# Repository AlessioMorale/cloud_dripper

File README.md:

# cloud_dripper
An ESP32-based indoor watering controller

Link to [Interactive BOM](https://htmlpreview.github.io/?https://github.com/AlessioMorale/cloud_dripper/blob/main/docs/index.html)

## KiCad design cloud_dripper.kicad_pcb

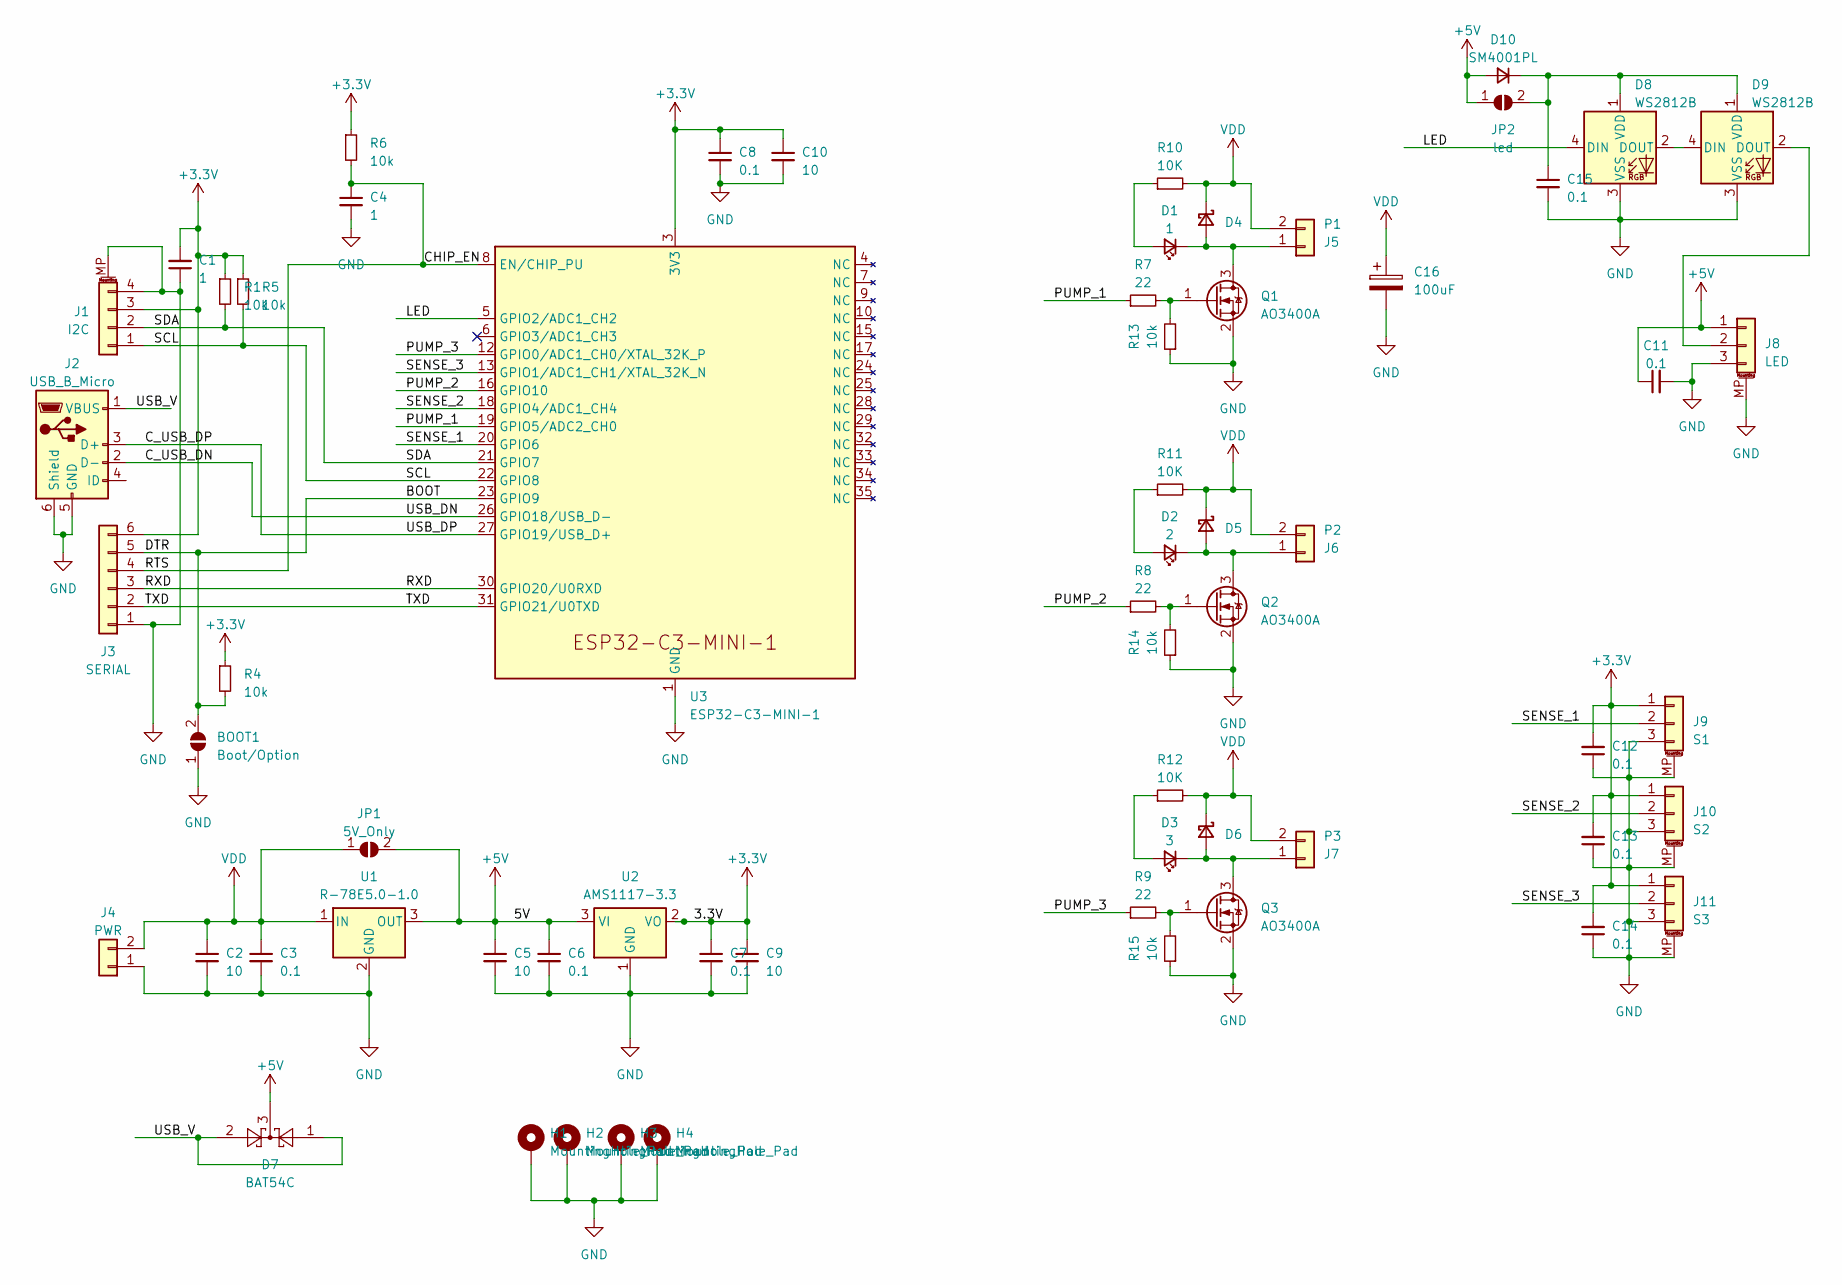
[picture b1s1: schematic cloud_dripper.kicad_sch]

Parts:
BOOT1: Boot/Option; SolderJumper-2_P1.3mm_Open_RoundedPad1.0x1.5mm
C1, C4: 1; C_0402_1005Metric; JLCPCB C52923
C2, C5, C9, C10: 10; C_0805_2012Metric; JLCPCB C15850
C3, C6, C7, C8, C11, C12, C13, C14, C15: 0.1; C_0402_1005Metric; JLCPCB C1525
C16: 100uF; CP_Elec_6.3x5.8
D1: 1; LED_0805_2012Metric; JLCPCB C2297
D2: 2; LED_0805_2012Metric; JLCPCB C2297
D3: 3; LED_0805_2012Metric; JLCPCB C2297
D4, D5, D6: D_SMA; JLCPCB C22452
D7: BAT54C; SOT-23
D8, D9: WS2812B; LED_WS2812B-2020_PLCC4_2.0x2.0mm
D10: SM4001PL; D_SOD-123F; JLCPCB C64898
H1, H2, H3, H4: MountingHole_Pad; MountingHole_2.2mm_M2_Pad
J1: I2C; JST_SH_BM04B-SRSS-TB_1x04-1MP_P1.00mm_Vertical
J2: USB_B_Micro; USB_Micro-B_Molex_47346-0001
J3: SERIAL; PinHeader_2x03_P2.54mm_Vertical
J4: PWR; Molex_Micro-Fit_3.0_43045-0200_2x01_P3.00mm_Horizontal
J5: P1; PinHeader_1x02_P2.54mm_Vertical
J6: P2; PinHeader_1x02_P2.54mm_Vertical
J7: P3; PinHeader_1x02_P2.54mm_Vertical
J8: LED; JST_SH_BM03B-SRSS-TB_1x03-1MP_P1.00mm_Vertical
J9: S1; JST_SH_BM03B-SRSS-TB_1x03-1MP_P1.00mm_Vertical
J10: S2; JST_SH_BM03B-SRSS-TB_1x03-1MP_P1.00mm_Vertical
J11: S3; JST_SH_BM03B-SRSS-TB_1x03-1MP_P1.00mm_Vertical
JP1: 5V_Only; SolderJumper-2_P1.3mm_Open_RoundedPad1.0x1.5mm
JP2: led; SolderJumper-2_P1.3mm_Open_RoundedPad1.0x1.5mm
Q1, Q2, Q3: AO3400A; SOT-23; JLCPCB C20917
R1, R4, R5, R6, R13, R14, R15: 10k; R_0402_1005Metric; JLCPCB C25744
R7, R8, R9: 22; R_0402_1005Metric; JLCPCB C25092
R10, R11, R12: 10K; R_0402_1005Metric; JLCPCB C25744
U1: R-78E5.0-1.0; Converter_DCDC_RECOM_R-78E-0.5_THT
U2: AMS1117-3.3; SOT-223-3_TabPin2; JLCPCB C6186
U3: ESP32-C3-MINI-1; JLCPCB C2838502

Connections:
+3.3V: C1.2, C7.1, C8.1, C9.1, C10.1, C12.2, C13.2, C14.2, J1.3, J3.6, J9.1, J10.1, J11.1, R1.1, R4.1, R5.1, R6.1, U2.2 (VO), U3.3 (3V3)
+5V: C5.1, C6.1, C11.1, D7.3, D10.2 (A), J8.1, JP1.2 (B), JP2.1 (A), U1.3 (OUT), U2.3 (VI)
/BOOT: BOOT1.2 (B), J3.5, R4.2, U3.23 (GPIO9)
/CHIP_EN: C4.1, J3.4, R6.2, U3.8 (EN/CHIP_PU)
/C_USB_DN: J2.2 (D-), U3.26 (GPIO18/USB_D-)
/C_USB_DP: J2.3 (D+), U3.27 (GPIO19/USB_D+)
/LED: D8.4 (DIN), U3.5 (GPIO2/ADC1_CH2)
/PUMP_1: R7.1, U3.19 (GPIO5/ADC2_CH0)
/PUMP_2: R8.1, U3.16 (GPIO10)
/PUMP_3: R9.1, U3.12 (GPIO0/ADC1_CH0/XTAL_32K_P)
/RXD: J3.3, U3.30 (GPIO20/U0RXD)
/SCL: J1.1, R5.2, U3.22 (GPIO8)
/SDA: J1.2, R1.2, U3.21 (GPIO7)
/SENSE_1: J9.2, U3.20 (GPIO6)
/SENSE_2: J10.2, U3.18 (GPIO4/ADC1_CH4)
/SENSE_3: J11.2, U3.13 (GPIO1/ADC1_CH1/XTAL_32K_N)
/TXD: J3.2, U3.31 (GPIO21/U0TXD)
/USB_V: D7.1, D7.2, J2.1 (VBUS)
GND: BOOT1.1 (A), C1.1, C2.2, C3.2, C4.2, C5.2, C6.2, C7.2, C8.2, C9.2, C10.2, C11.2, C12.1, C13.1, C14.1, C15.2, C16.2, D8.3 (VSS), D9.3 (VSS), H1.1, H2.1, H3.1, H4.1, J1.4, J1.MP (MountPin), J2.5 (GND), J2.6 (Shield), J3.1, J4.1, J8.3, J8.MP (MountPin), J9.3, J9.MP (MountPin), J10.3, J10.MP (MountPin), J11.3, J11.MP (MountPin), Q1.2 (S), Q2.2 (S), Q3.2 (S), R13.1, R14.1, R15.1, U1.2 (GND), U2.1 (GND), U3.1 (GND), U3.2 (GND), U3.11 (GND), U3.14 (GND), U3.36 (GND), U3.37 (GND), U3.38 (GND), U3.39 (GND), U3.40 (GND), U3.41 (GND), U3.42 (GND), U3.43 (GND), U3.44 (GND), U3.45 (GND), U3.46 (GND), U3.47 (GND), U3.48 (GND), U3.49 (GND), U3.50 (GND), U3.51 (GND), U3.52 (GND), U3.53 (GND)
unnamed: D1.2 (A), R10.1
unnamed: D1.1 (K), D4.2 (A), J5.1, Q1.3 (D)
unnamed: D2.2 (A), R11.1
unnamed: D2.1 (K), D5.2 (A), J6.1, Q2.3 (D)
unnamed: D3.2 (A), R12.1
unnamed: D3.1 (K), D6.2 (A), J7.1, Q3.3 (D)
unnamed: D8.2 (DOUT), D9.4 (DIN)
unnamed: D9.2 (DOUT), J8.2
unnamed: C15.1, D8.1 (VDD), D9.1 (VDD), D10.1 (K), JP2.2 (B)
unnamed: Q1.1 (G), R7.2, R13.2
unnamed: Q2.1 (G), R8.2, R14.2
unnamed: Q3.1 (G), R9.2, R15.2
VDD: C2.1, C3.1, C16.1, D4.1 (K), D5.1 (K), D6.1 (K), J4.2, J5.2, J6.2, J7.2, JP1.1 (A), R10.2, R11.2, R12.2, U1.1 (IN)

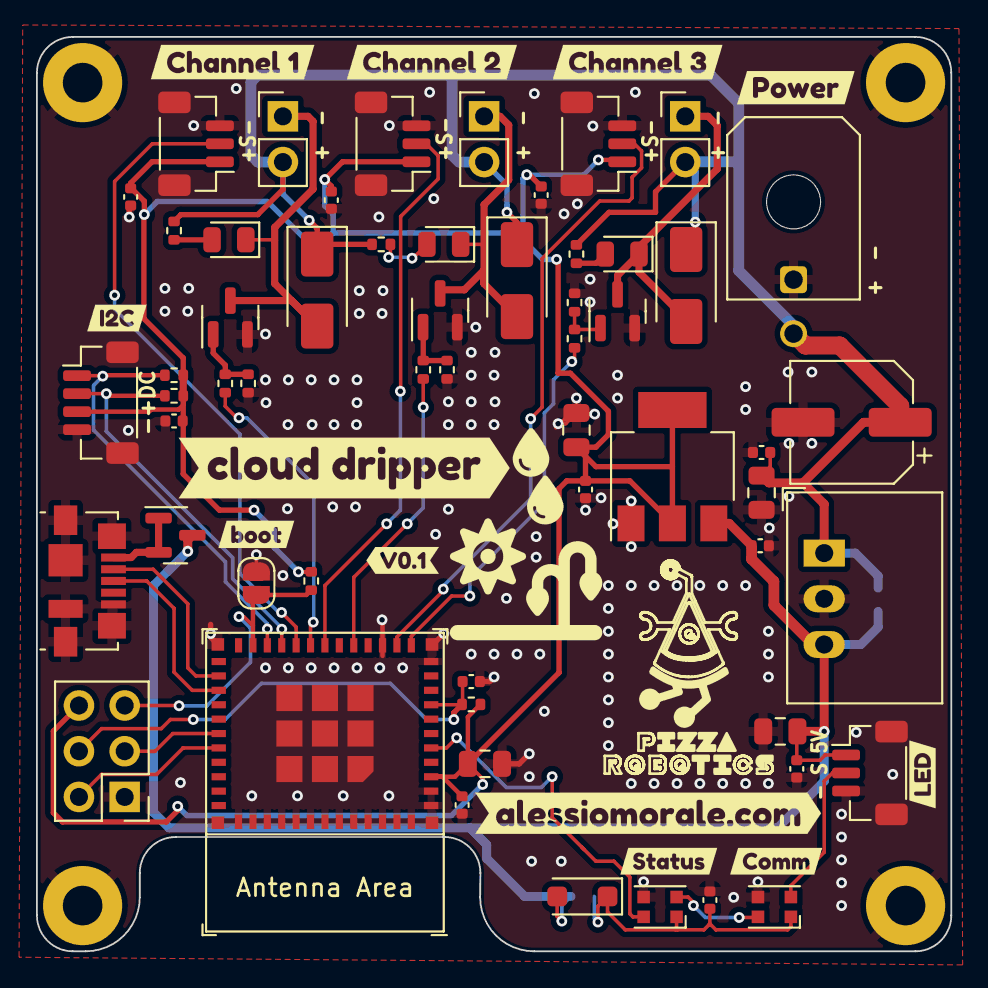
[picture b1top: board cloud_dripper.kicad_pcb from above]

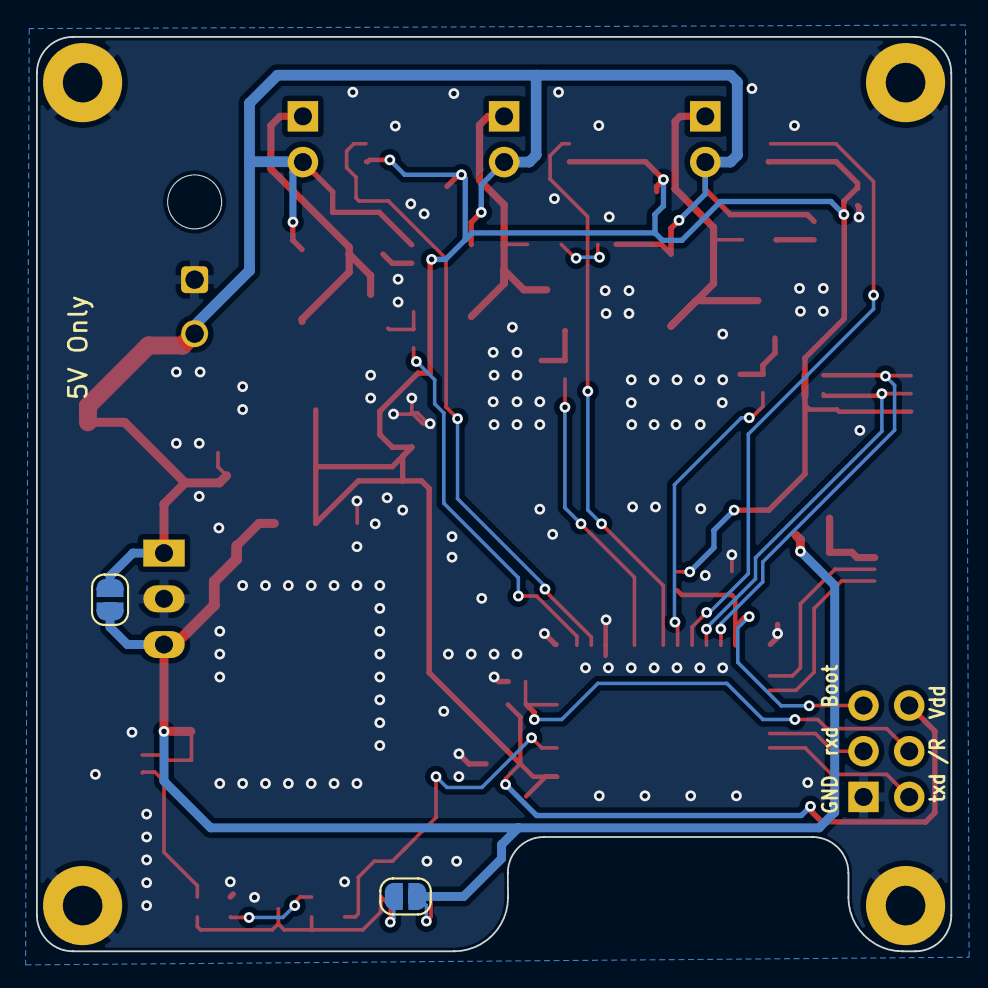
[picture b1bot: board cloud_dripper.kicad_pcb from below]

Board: 2 copper layers, 50.8 x 50.8 mm, 75 parts (2 on the bottom side), 32 nets.

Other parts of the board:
kibuzzard-63F0DE5A: G***; kibuzzard-63F0DE5A
kibuzzard-63F0DE6D: G***; kibuzzard-63F0DE6D
kibuzzard-63F0DE63: G***; kibuzzard-63F0DE63
kibuzzard-63F0DE78: G***; kibuzzard-63F0DE78
kibuzzard-63F0E3D4: G***; kibuzzard-63F0E3D4
kibuzzard-63F2BAAA: G***; kibuzzard-63F2BAAA
kibuzzard-63F29C45: G***; kibuzzard-63F29C45
kibuzzard-63F29C55: G***; kibuzzard-63F29C55
kibuzzard-63F29CEB: G***; kibuzzard-63F29CEB
kibuzzard-63F11438: G***; kibuzzard-63F11438
kibuzzard-63F11462: G***; kibuzzard-63F11462
kibuzzard-63F11506: G***; kibuzzard-63F11506

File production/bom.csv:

Designator,Footprint,Quantity,Value,LCSC Part #
BOOT1,SolderJumper-2_P1.3mm_Open_RoundedPad1.0x1.5mm,1,Boot/Option,
C1,0402,1,1,
C10,0805,1,10,
C11,0402,1,0.1,
C12,0402,1,0.1,
C13,0402,1,0.1,
C14,0402,1,0.1,
C15,0402,1,0.1,
C16,CP_Elec_6.3x5.8,1,100uF,
C2,0805,1,10,
C3,0402,1,0.1,
C4,0402,1,1,
C5,0805,1,10,
C6,0402,1,0.1,
C7,0402,1,0.1,
C8,0402,1,0.1,
C9,0805,1,10,
D1,0805,1,1,
D10,D_SOD-123F,1,SM4001PL,
D2,0805,1,2,
D3,0805,1,3,
"D4, D5, D6",D_SMA,3,~,
D7,SOT-23,1,BAT54C,
"D8, D9",LED_WS2812B-2020_PLCC4_2.0x2.0mm,2,WS2812B,
"H1, H2, H3, H4",MountingHole_2.2mm_M2_Pad,4,MountingHole_Pad,
J1,JST_SH_BM04B-SRSS-TB_1x04-1MP_P1.00mm_Vertical,1,I2C,
J10,JST_SH_BM03B-SRSS-TB_1x03-1MP_P1.00mm_Vertical,1,S2,
J11,JST_SH_BM03B-SRSS-TB_1x03-1MP_P1.00mm_Vertical,1,S3,
J2,USB_Micro-B_Molex_47346-0001,1,USB_B_Micro,
J3,PinHeader_2x03_P2.54mm_Vertical,1,SERIAL,
J4,Molex_Micro-Fit_3.0_43045-0200_2x01_P3.00mm_Horizontal,1,PWR,
J5,PinHeader_1x02_P2.54mm_Vertical,1,P1,
J6,PinHeader_1x02_P2.54mm_Vertical,1,P2,
J7,PinHeader_1x02_P2.54mm_Vertical,1,P3,
J8,JST_SH_BM03B-SRSS-TB_1x03-1MP_P1.00mm_Vertical,1,LED,
J9,JST_SH_BM03B-SRSS-TB_1x03-1MP_P1.00mm_Vertical,1,S1,
JP1,SolderJumper-2_P1.3mm_Open_RoundedPad1.0x1.5mm,1,5V_Only,
JP2,SolderJumper-2_P1.3mm_Open_RoundedPad1.0x1.5mm,1,led,
"Q1, Q2, Q3",SOT-23,3,AO3400A,
R1,0402,1,10k,
R10,0402,1,10K,
R11,0402,1,10K,
R12,0402,1,10K,
R13,0402,1,10k,
R14,0402,1,10k,
R15,0402,1,10k,
R4,0402,1,10k,
R5,0402,1,10k,
R6,0402,1,10k,
R7,0402,1,22,
R8,0402,1,22,
R9,0402,1,22,
U1,Converter_DCDC_RECOM_R-78E-0.5_THT,1,R-78E5.0-1.0,
U2,SOT-223-3_TabPin2,1,AMS1117-3.3,
U3,ESP32-C3-MINI-1,1,ESP32-C3-MINI-1,

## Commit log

2023-02-20 feat: Initial version - sent to fab.
